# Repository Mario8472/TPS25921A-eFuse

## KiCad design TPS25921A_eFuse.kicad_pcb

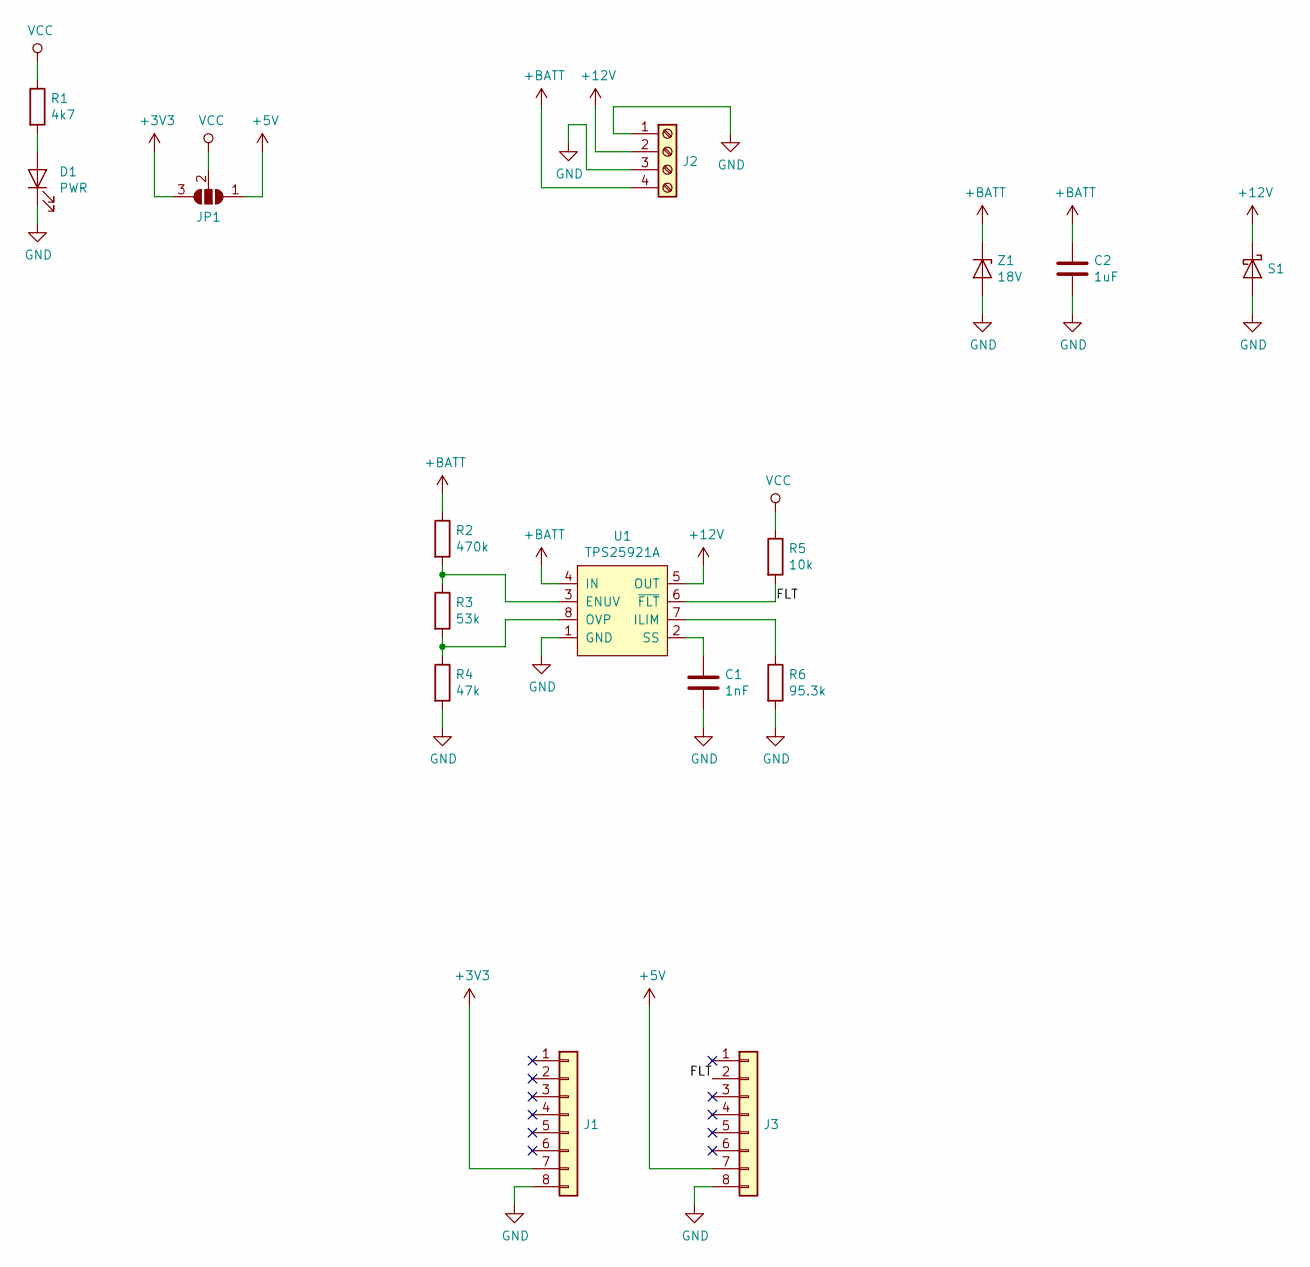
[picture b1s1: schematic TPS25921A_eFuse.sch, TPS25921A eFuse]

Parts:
C1: 1nF; C_0805_2012Metric
C2: 1uF; C_1206_3216Metric
D1: PWR; LED_0805_2012Metric
J1, J3: Conn_01x08; PinHeader_1x08_P2.54mm_Vertical
J2: Screw_Terminal_01x04; PCB_Screw_Terminal_5.08_4ways
JP1: SolderJumper_3_Open; Jumper_0805
R1: 4k7; R_0805_2012Metric
R2: 470k; R_0805_2012Metric
R3: 53k; R_0805_2012Metric
R4: 47k; R_0805_2012Metric
R5: 10k; R_0805_2012Metric
R6: 95.3k; R_0805_2012Metric
S1: D_Schottky; D_SMA
U1: TPS25921A; SOIC-8_3.9x4.9mm_P1.27mm
Z1: 18V; D_SMA

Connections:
+3V3: J1.7, JP1.3 (B)
+5V: J3.7, JP1.1 (A)
+12V: J2.2, S1.1 (K), U1.5 (OUT)
+BATT: C2.1, J2.4, R2.1, U1.4 (IN), Z1.1 (K)
/FLT: J3.2, R5.2, U1.6 (~FLT)
GND: C1.2, C2.2, D1.1 (K), J1.8, J2.1, J2.3, J3.8, R4.2, R6.2, S1.2 (A), U1.1 (GND), Z1.2 (A)
unnamed: C1.1, U1.2 (SS)
unnamed: D1.2 (A), R1.2
unnamed: R2.2, R3.1, U1.3 (ENUV)
unnamed: R3.2, R4.1, U1.8 (OVP)
unnamed: R6.1, U1.7 (ILIM)
VCC: JP1.2 (C), R1.1, R5.1

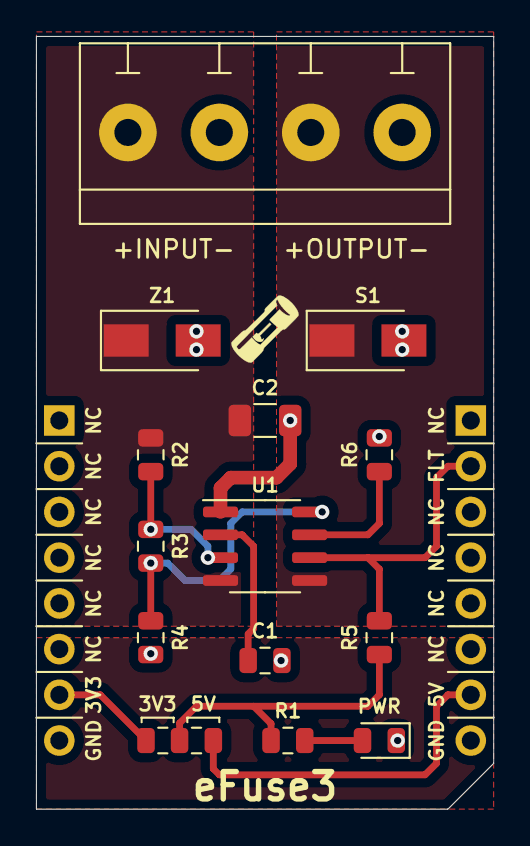
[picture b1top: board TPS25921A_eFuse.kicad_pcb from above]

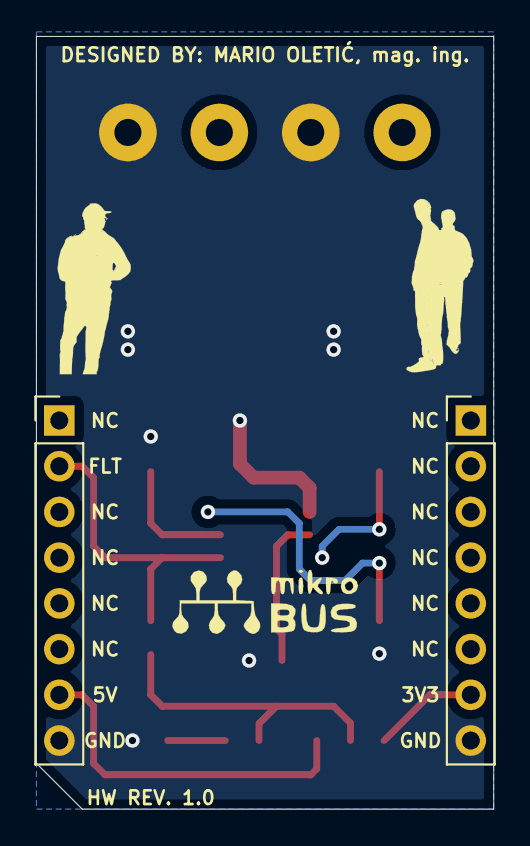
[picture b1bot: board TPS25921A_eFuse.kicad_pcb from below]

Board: 2 copper layers, 25.4 x 42.9 mm, 16 parts (2 on the bottom side), 12 nets.
